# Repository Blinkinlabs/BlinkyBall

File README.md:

# Circuit and code for a heartbeat bouncy ball

## License

This design, including the software and hardware, is licensed under the MIT license.

## PCB Design

The PCB design is made in Cadsoft Eagle 7.1 (http://www.cadsoftusa.com/download-eagle/).
The free version should be fine for opening and editing the design.

It's based on the Atmel ATTINY85, though an ATTINY45 or ATTINY25 would probably also work.

## Firmware

The firmware is written against avr-gcc.

### Toolchain setup for OS X

Install XCode and command line tools. Version 6.1.1 was used for development, but this should
not be critical. The method for enabling the command line tools seems to be a moving target,
one set of instructions is here (https://developer.apple.com/library/ios/technotes/tn2339/_index.html).

Install CrossPack for AVR (http://www.obdev.at/products/crosspack/download.html). Version
CrossPack-AVR 20130212 was used for development. Most likey this code is not version-sensitive.

### Compiling

Once the toolchain is configured, this should be as simple as:

  make
  
### Uploading firmware

An AVR ISP is required to upload code. The Makefile is configured to use a USBTinyISP
(https://learn.adafruit.com/usbtinyisp), however it would be trivial to use a different
one, or even an Arduino to upload the code.

Solder the 6 ICSP test points on the board (use Eagle to inspect the pinout- the board design
is a moving target), then an automatic upload should work:

  make install

A test jig can also be built to make code upload possible without soldering.

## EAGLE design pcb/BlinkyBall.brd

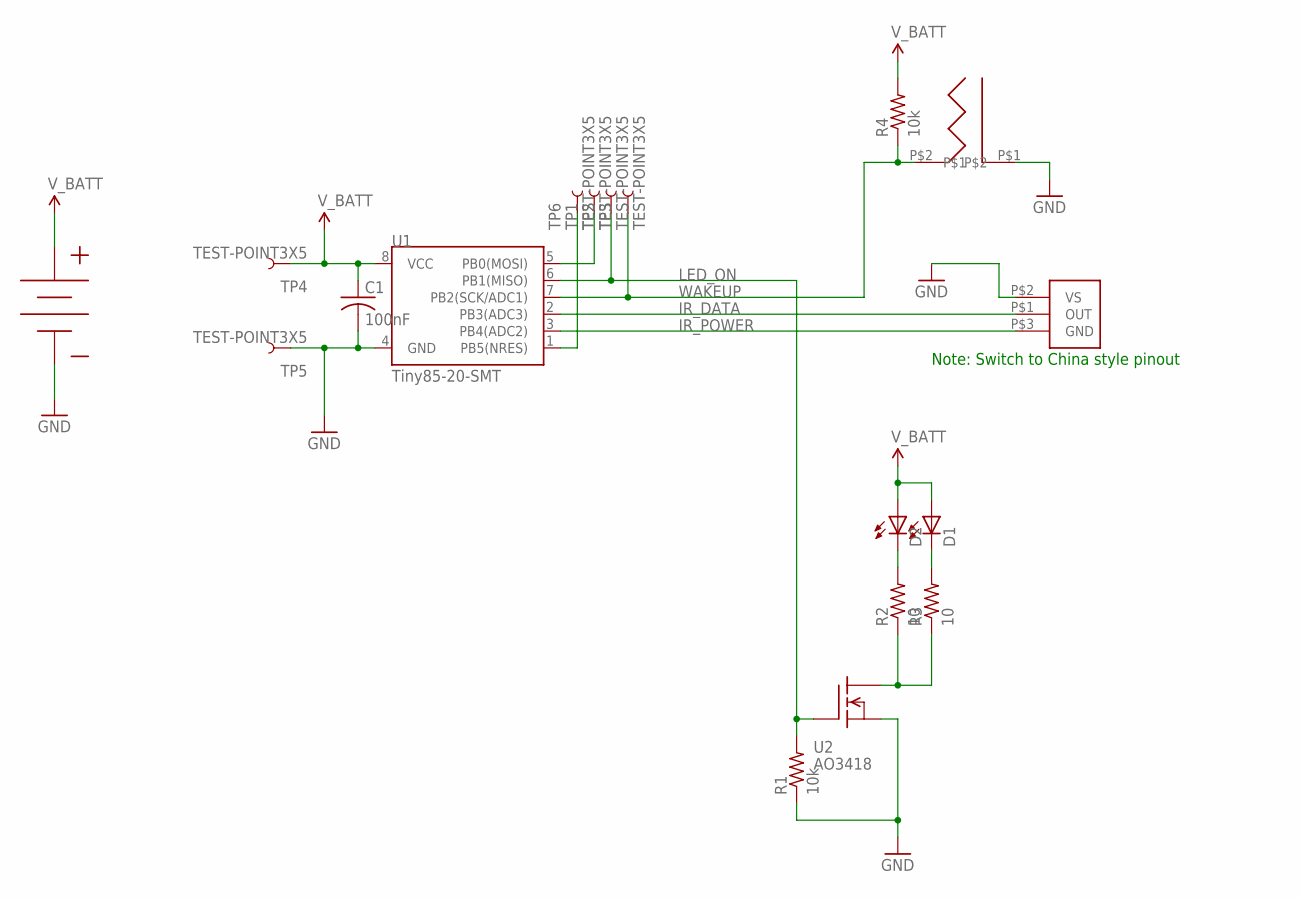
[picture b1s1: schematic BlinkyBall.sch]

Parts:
C1: 100nF; C0603
D1, D2: LED5MM
J1: SW-18015P
J2: BATTERY_BUTTON_CELLAG3; BATTERY_COVER_AG3
R1, R4: 10k; R0603
R2, R3: 10; R0603
TP1, TP2, TP3, TP4, TP5, TP6: TEST-POINT3X5; PAD.03X.05
U1: Tiny85-20-SMT; SO08-EIAJ
U2: AO3418; SOT23
U3: TSOP321

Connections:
GND: C1.2, J1.P$1, J2.-, R1.1, TP5.P$1, U1.4 (GND), U2.2 (S), U3.P$2 (VS)
IR_DATA: U1.2 (PB3(ADC3)), U3.P$1 (OUT)
IR_POWER: U1.3 (PB4(ADC2)), U3.P$3 (GND)
LED_ON: R1.2, TP2.P$1, U1.6 (PB1(MISO)), U2.1 (G)
unnamed: D2.K (C), R2.2
unnamed: D1.K (C), R3.2
unnamed: R2.1, R3.1, U2.3 (D)
RESET: TP6.P$1, U1.1 (PB5(NRES))
V_BATT: C1.1, D1.A, D2.A, J2.+1 (+), J2.+2 (+), J2.+3 (+), J2.+4 (+), R4.2, TP4.P$1, U1.8 (VCC)
WAKEUP: J1.P$2, R4.1, TP3.P$1, U1.7 (PB2(SCK/ADC1))
YYYYY: TP1.P$1, U1.5 (PB0(MOSI))

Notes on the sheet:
Note: Switch to China style pinout

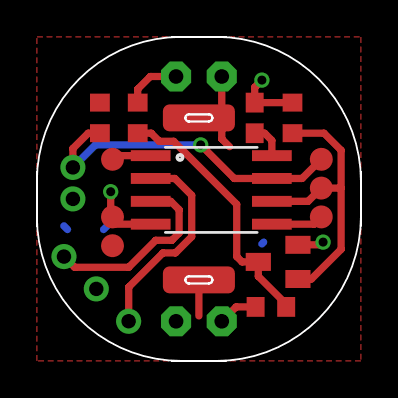
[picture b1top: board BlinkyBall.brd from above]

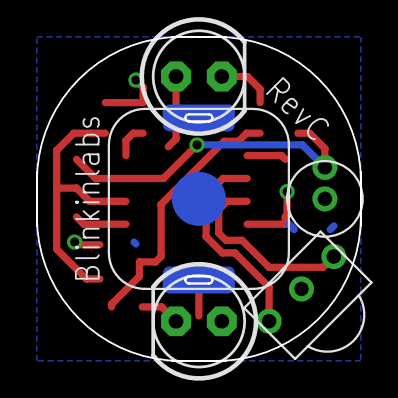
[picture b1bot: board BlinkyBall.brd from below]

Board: 2 copper layers, 18.0 x 18.0 mm, 18 parts (5 on the bottom side), 11 nets.

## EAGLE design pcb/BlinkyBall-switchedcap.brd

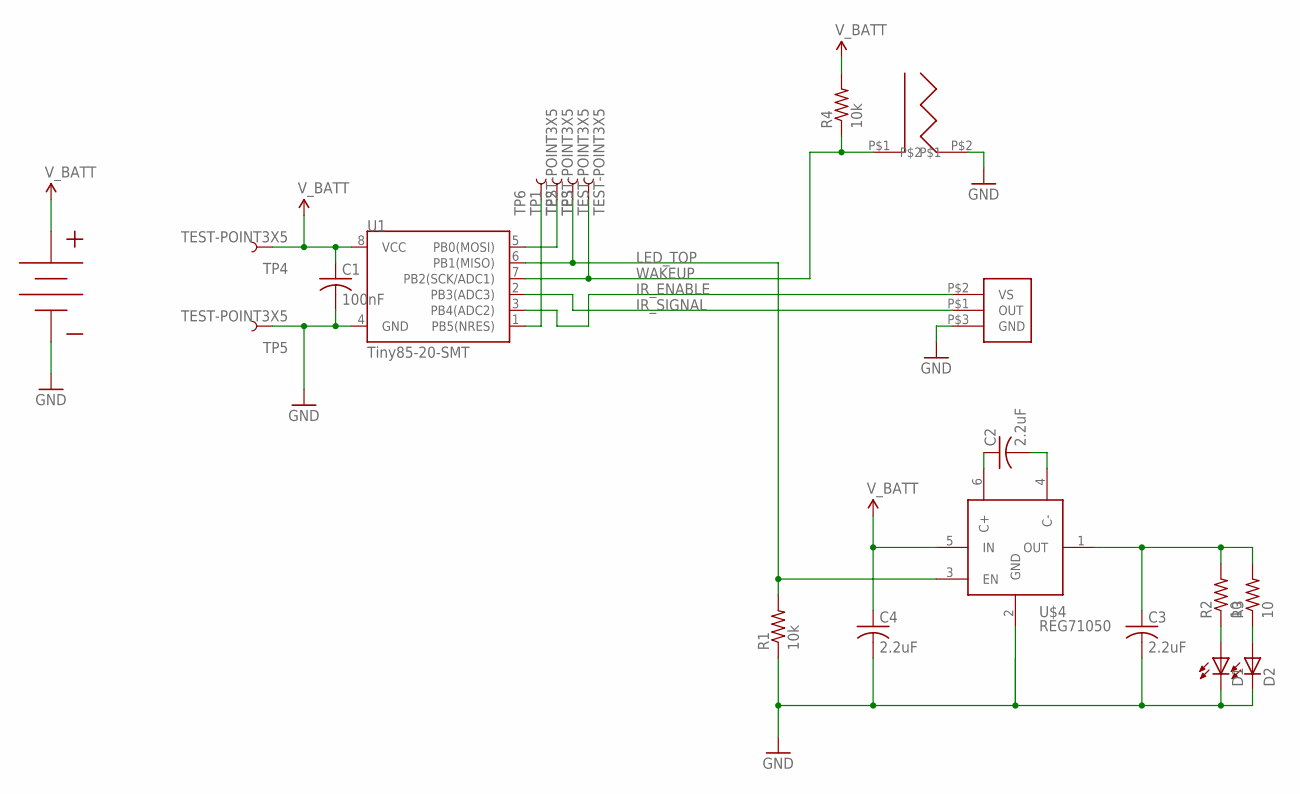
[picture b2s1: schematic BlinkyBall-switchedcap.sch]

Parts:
C1: 100nF; C0603
C2, C3, C4: 2.2uF; C0603
D1, D2: LED5MM
R1, R4: 10k; R0603
R2, R3: 10; R0603
TP1, TP2, TP3, TP4, TP5, TP6: TEST-POINT3X5; PAD.03X.05
U1: Tiny85-20-SMT; SO08-EIAJ
U$1: BATTERY_BUTTON_CELLAG3; BATTERY_COVER_AG3
U$3: SW-18015P
U$4: REG71050; SOT23-6
U$5: TSOP321

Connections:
GND: C1.2, C3.2, C4.2, D1.K (C), D2.K (C), R1.1, TP5.P$1, U1.4 (GND), U$1.-, U$3.P$2, U$4.2 (GND), U$5.P$3 (GND)
IR_ENABLE: U1.3 (PB4(ADC2)), U$5.P$2 (VS)
IR_SIGNAL: U1.2 (PB3(ADC3)), U$5.P$1 (OUT)
LED_TOP: R1.2, TP2.P$1, U1.6 (PB1(MISO)), U$4.3 (EN)
unnamed: D2.A, R3.1
unnamed: D1.A, R2.1
unnamed: C2.1, U$4.6 (C+)
unnamed: C2.2, U$4.4 (C-)
unnamed: C3.1, R2.2, R3.2, U$4.1 (OUT)
RESET: TP6.P$1, U1.1 (PB5(NRES))
V_BATT: C1.1, C4.1, R4.2, TP4.P$1, U1.8 (VCC), U$1.+1 (+), U$1.+2 (+), U$1.+3 (+), U$1.+4 (+), U$4.5 (IN)
WAKEUP: R4.1, TP3.P$1, U1.7 (PB2(SCK/ADC1)), U$3.P$1
YYYYY: TP1.P$1, U1.5 (PB0(MOSI))

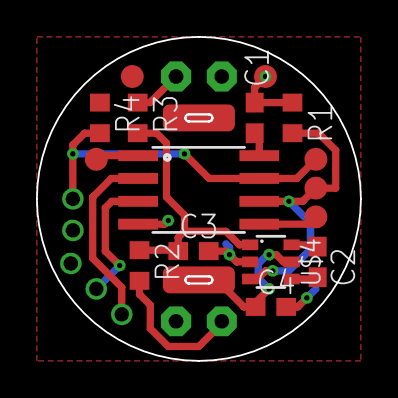
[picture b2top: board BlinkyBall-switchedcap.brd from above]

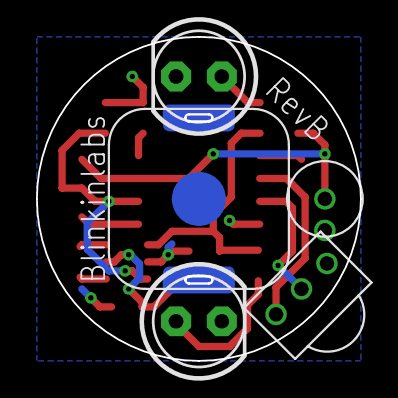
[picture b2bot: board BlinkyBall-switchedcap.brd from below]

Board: 2 copper layers, 18.0 x 18.0 mm, 21 parts (5 on the bottom side), 13 nets.

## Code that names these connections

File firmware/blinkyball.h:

#ifndef BLINKYBALL_H_
#define BLINKYBALL_H_

// Define pins
#define PIN_LED_ON      PB1     // LED control pin; pulled low externally
#define PIN_WAKEUP      PB2     // Wakeup pin; pulled high externally
#define PIN_IR_POWER    PB4     // IR Power supply
#define PIN_IR_DATA     PB3     // IR Data input

#define PIN_UNUSED      PB0     // Unused pin; should configure as pull-up

// System parameters
#define IR_MONITOR_TIME         20  // Amount of time to stay awake for IR reception, in 10ths of a second

#define DEBOUNCE_COUNT_DEFAULT   20 // Wakeup sensitivity, in counts (higher is less sensitive)
#define REPEAT_COUNT_DEFAULT      1 // Repeat count in 7-pulse units
#define HEARTBEAT_SPEED_DEFAULT 140 // Heartbeat speed in units

#define REPEAT_COUNT_MAXIMUM      4 // Maximum repeat counts
#define REPEAT_COUNT_MINIMUM      1 // Minimum repeat counts
#define DEBOUNCE_COUNT_MAXIMUM  120 // Maximum debounce count
#define DEBOUNCE_COUNT_MINIMUM   15 // Minimum debounce count
#define HEARTBEAT_SPEED_MINIMUM  50 // Mimimum heartbeat speed, 170 BPM
#define HEARTBEAT_SPEED_MAXIMUM 240 // Mimimum heartbeat speed, 35 BPM


// EEPROM data addresses
#define MAGIC_HEADER_ADDRESS    0
#define DEBOUNCE_COUNT_ADDRESS  1
#define REPEAT_COUNT_ADDRESS    2
#define HEARTBEAT_SPEED_ADDRESS 3

// Magic header to determine if the EEPROM was written properly
#define  MAGIC_HEADER_VALUE     0xDE

//#define SERIAL_DEBUG

#define bitSet(reg, bit) reg |= (1<<bit)
#define bitClear(reg, bit) reg &= ~(1<<bit)

#define setLEDs(value) OCR1A = value

#include <avr/io.h>
#include <util/delay.h>

void pulseOut(uint8_t data);
uint8_t measureBattery();

#endif

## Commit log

2015-01-17 RevA board design
2015-01-17 Working towards RevB board design: Smaller, more vertical
2015-01-17 Add flashy firmware
2015-01-17 Add real-life EKG pulse
2015-01-19 RevB pcb- transistor switch for LEDs
2015-01-19 Add switched-cap design for potential power boost
2015-01-19 Display solid pattern for LED evaluation
2015-01-19 Add debounce feature to reduce turn-on sensitivity
2015-01-19 Move PCB designs to their own directory
2015-01-22 New EKG function from Kyle, repeat count
2015-01-22 Switch to c++ compiler, use timer1 for LED PWM
2015-01-22 RevC pcb design: rounded rect, switch IR pinout, space out test points
2015-01-22 More design tweaks
2015-01-22 RevC, as submitted for production
2015-01-26 Modify Makefile (still not sensitive to .h changes)
2015-01-26 PCB: Fix referene names
2015-01-26 Push config values into the EEPROM, don't erase EEPROM during flash cycles
2015-01-26 Correct pinout for IR receiver
2015-01-27 Still nonworking IR
2015-01-27 Ir works???!!!
2015-01-27 Tighten up timing requirements
2015-01-27 Intersperse IR readings with LED output
2015-01-27 Push LED frequency back to 32KHz
2015-01-27 Bugfix: used too much RAM
2015-01-27 IR works: ran out of memory, so disable interrupts during intensive operations
2015-01-27 Disable debug outputs
2015-01-27 Add arduino programmer example
2015-01-27 Add blink simulator for Arduino Uno
2015-01-27 Less bright LEDs for IR reception conformation
2015-01-28 Separate clock speeds for programming fuses, to work with fresh chips
2015-01-28 Switch to C for much lower processing demands
2015-01-28 Use 7 flashes pattern
2015-01-28 Capitalize IRremote libray filenames, move IRremote into separate function
2015-01-28 Remove old EKG effect
2015-01-28 Update programmer example
2015-01-28 Drop back to 4MHz
2015-01-29 Add repeat count function back in
2015-01-29 More tweaks
2015-01-29 Improve voltage scaling design
2015-01-29 Add .9 firmware, test rig script
2015-01-29 Adjust timings, disable voltage scaling (boo!)
2015-01-29 Double-check heartbeat speeds (look fine)
2015-01-29 Lower IR reception window to 2 seconds
2015-01-29 Add guard bands on the settings
2015-01-29 Potential 1.0 release
2015-01-29 Add a 2 second watchdog, that's kicked in the playback and IR routines.
2015-01-30 1.0 release
2015-01-30 Change sensitivity to 100 in arduino program, and add verify function to Makefile
2015-01-30 Update fuse setting
2017-05-27 Fixes for case-sensitive file system
2017-10-25 Remove old schematic design, add release files for production version
2017-10-25 Add public license and documentation photo

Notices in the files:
parts and their libraries:
SparkFun-DigitalIC: Licensing: CC v3.0 Share-Alike You are welcome to use this library for commercial purposes.
